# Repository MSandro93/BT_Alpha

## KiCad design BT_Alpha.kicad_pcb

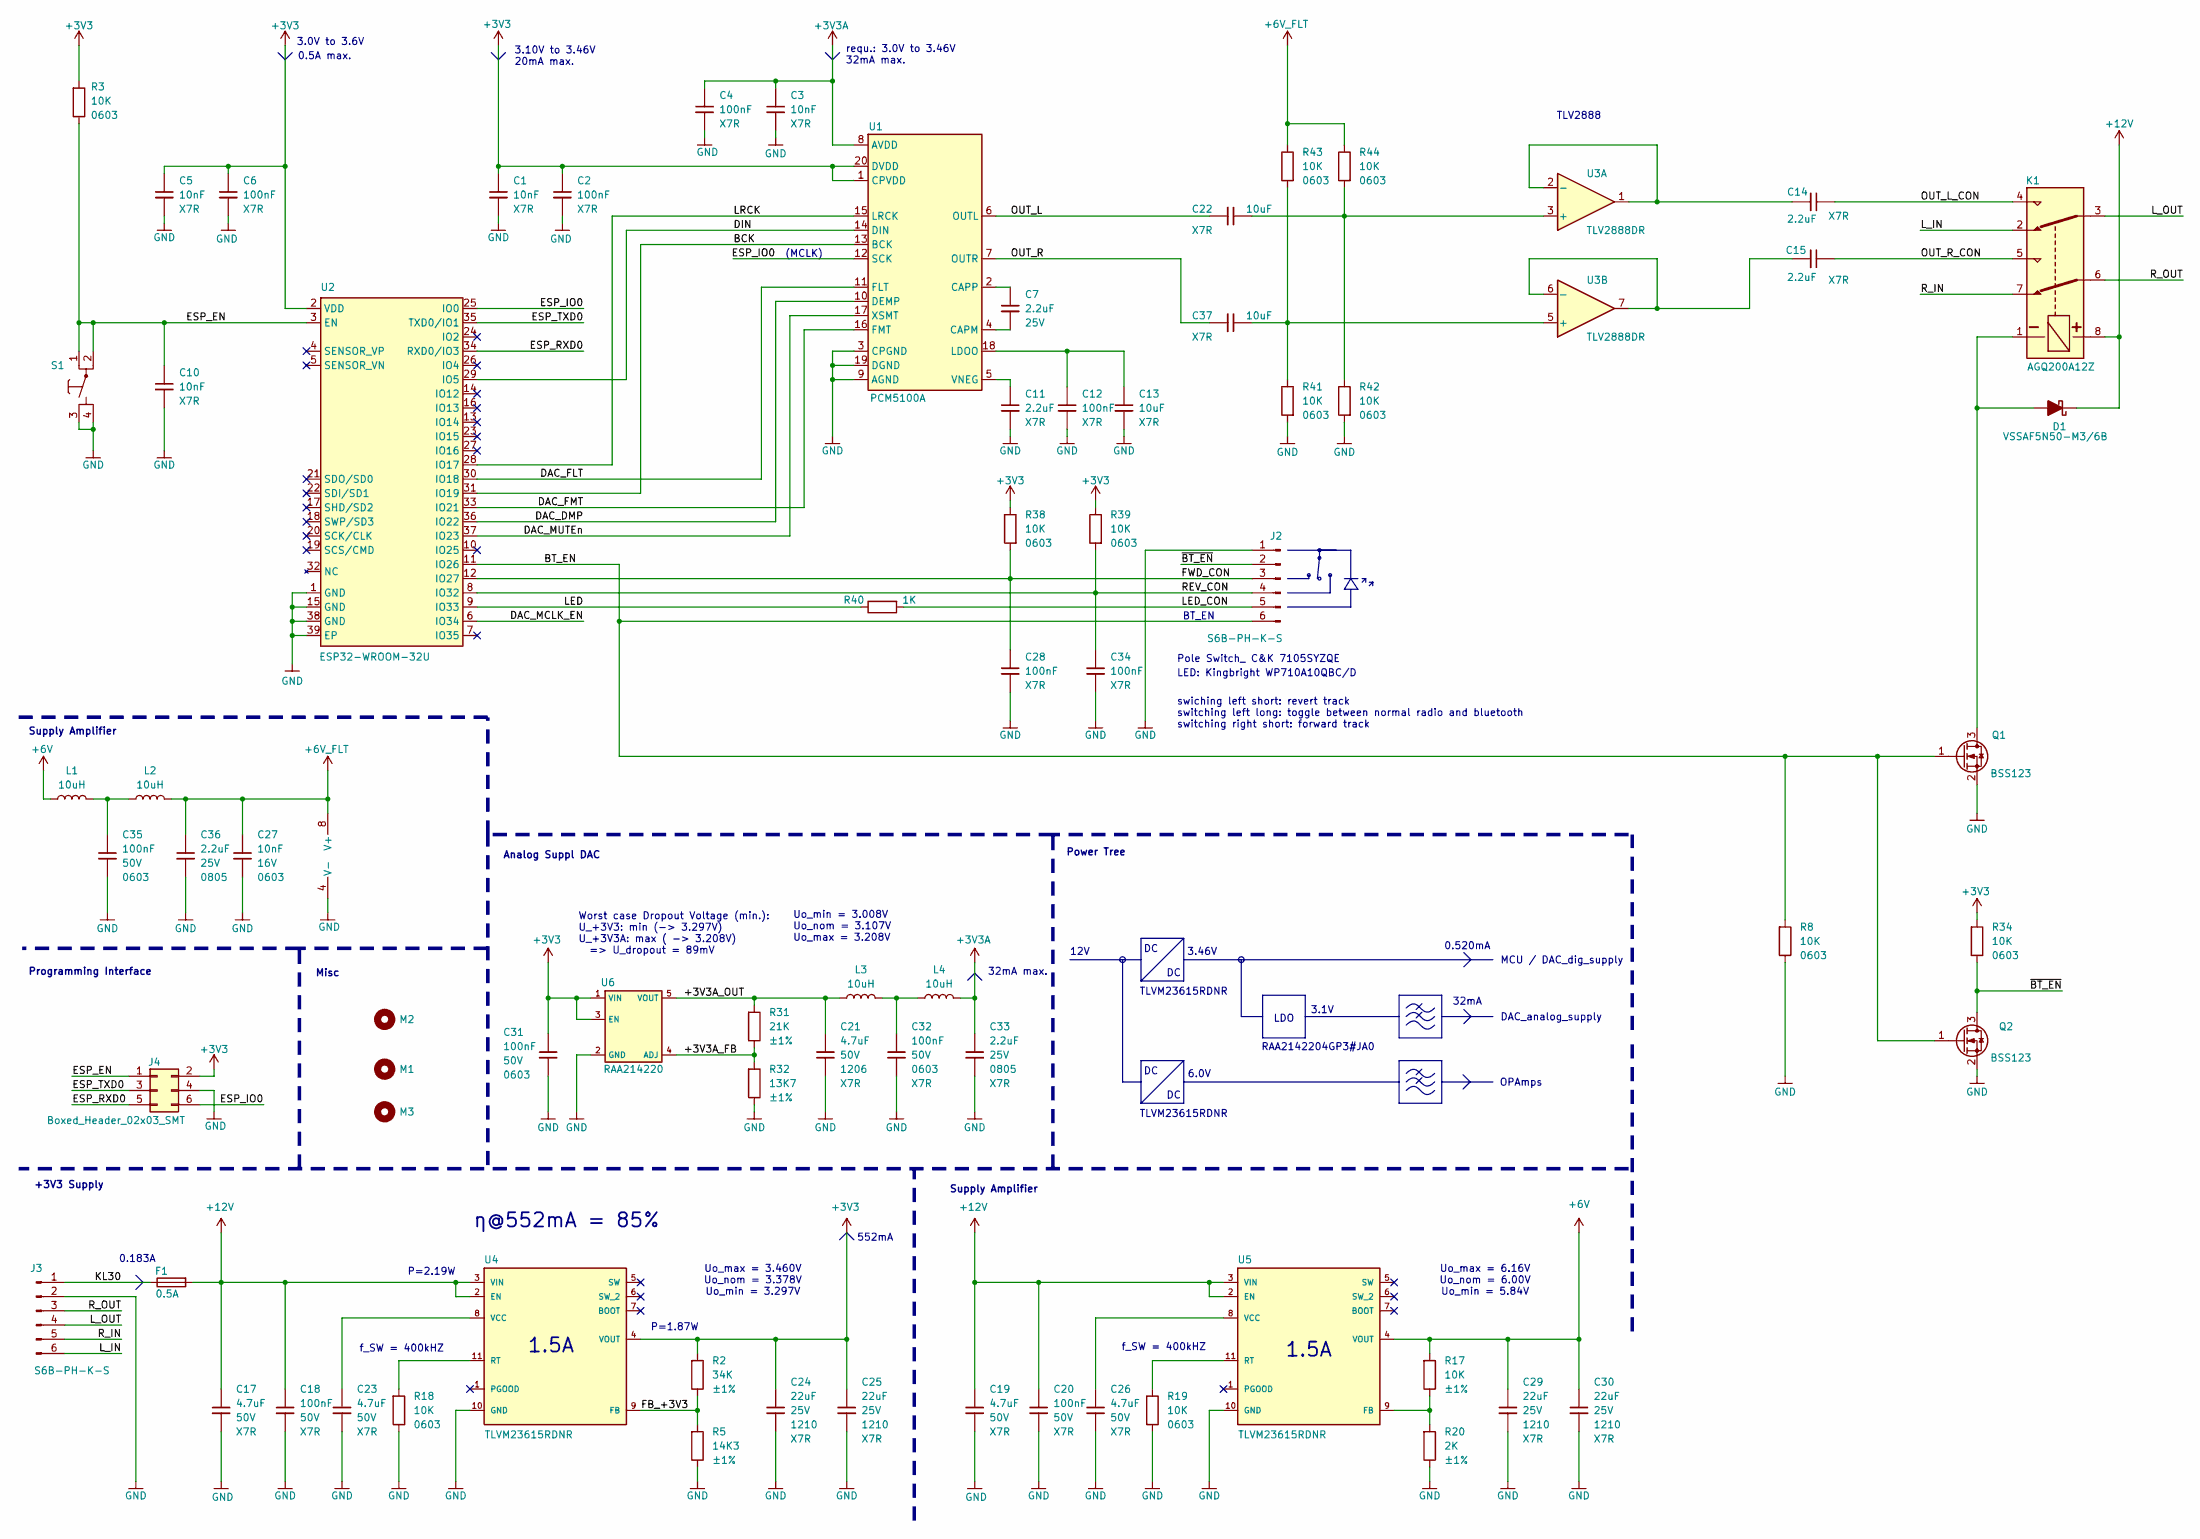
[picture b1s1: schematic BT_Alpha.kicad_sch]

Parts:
C1, C3, C5, C10, C27: 10nF; C_0603; Voltage 16V; Voltage [V] 16; Manufacturer Part Number 0603YC103KAT2A
C2, C4, C6, C12, C18, C20, C28, C31, C32, C34, C35: 100nF; C_0603; Voltage 50V; Voltage [V] 50; Manufacturer Part Number CL10B104KB8NNNC
C7, C11, C14, C15, C33, C36: 2.2uF; C_0805; Voltage 25V; Voltage [V] 25; Manufacturer Part Number CL21B225KAFNNNE
C13, C22, C37: 10uF; C_0805; Voltage 16V; Voltage [V] 16; Manufacturer Part Number CL21B106KOQNNNG
C17, C19, C21, C23, C26: 4.7uF; C_1206; Voltage 50V; Voltage [V] 50; Manufacturer Part Number CL31B475KBHNNNE
C24, C25, C29, C30: 22uF; C_1210; Voltage 25V; Voltage [V] 25; Manufacturer Part Number CL32B105KAFNNNE
D1: VSSAF5N50-M3/6B; VSSAF5N50; Voltage 0.56V; Voltage [V] 0.56; Manufacturer Part Number VSSAF5N50-M3/6B
F1: SF-1206S050-2; SF-1206S; Voltage [V] 63; Voltage 63VDC; Manufacturer Part Number SF-1206S050-2
J2, J3: S6B-PH-K-S; Manufacturer Part Number S6B-PH-K-S
J4: Boxed_Header_02x03_SMT
K1: AGQ200A12Z; AGQ200Axxx; Voltage [V] 12; Voltage 12V; Manufacturer Part Number AGQ200A12Z
L1, L2, L3, L4: 10uH; 74479777310; Manufacturer Part Number 74479777310
M1, M2, M3: Mounting_Hole_2.7mm_Unplated
Q1, Q2: BSS123; Voltage 100V; Voltage [V] 100; Manufacturer Part Number BSS123
R2: 34K; R_0603; Voltage 150V; Voltage [V] 150; Manufacturer Part Number RC0603FR-0734KL
R3, R8, R17, R18, R19, R34, R38, R39, R41, R42, R43, R44: 10K; R_0603; Voltage 150V; Voltage [V] 150; Manufacturer Part Number RC0603FR-0710KL
R5: 14K3; R_0603; Voltage 150V; Voltage [V] 150; Manufacturer Part Number RC0603FR-0714K3L
R20: 2K; R_0603; Voltage 150V; Voltage [V] 150; Manufacturer Part Number RC0603FR-0714K3L
R31: 21K; R_0603; Voltage 150V; Voltage [V] 150; Manufacturer Part Number RC0603FR-0721KL
R32: 13K7; R_0603; Voltage 150V; Voltage [V] 150; Manufacturer Part Number RC0603FR-0713K7L
R40: 1K; R_0603; Voltage 150V; Voltage [V] 150; Manufacturer Part Number RC0603FR-071KL
S1: 434123025826; Manufacturer Part Number 434123025826
U1: PCM5100A; PCM510xx; Manufacturer Part Number PCM5100A
U2: ESP32-WROOM-32U; WROOM_32U; Voltage 3.0 - 3.6; Voltage [V] 3.0V - 3.6V; Manufacturer Part Number ESP32-WROOM-32UE-N8
U3: TLV2888DR; Manufacturer Part Number TLV2888DR
U4, U5: TLVM23615RDNR; TxxM336x5; Manufacturer Part Number TLVM23615RDNR
U6: RAA214220; Manufacturer Part Number RAA2142204GP3#JA0

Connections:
+3V3: C1.1, C2.1, C5.1, C6.1, C24.1, C25.1, C31.1, J4.2, R2.1, R3.1, R34.1, R38.2, R39.2, U1.1 (CPVDD), U1.20 (DVDD), U2.2 (VDD), U4.4 (VOUT), U6.1 (VIN), U6.3 (EN)
+3V3A: C3.1, C4.1, C33.1, L4.2, U1.8 (AVDD)
+6V: C29.1, C30.1, L1.1, R17.1, U5.4 (VOUT)
+6V_FLT: C27.1, C36.1, L2.2, R43.2, R44.2, U3.8 (V+)
+12V: C17.1, C18.1, C19.1, C20.1, D1.K, F1.1, K1.8, U4.2 (EN), U4.3 (VIN), U5.2 (EN), U5.3 (VIN)
/+3V3A_FB: R31.2, R32.1, U6.4 (ADJ)
/+3V3A_OUT: C21.1, L3.1, R31.1, U6.5 (VOUT)
/BCK: U1.13 (BCK), U2.31 (IO19)
/BT_EN: J2.6, Q1.1 (G), Q2.1 (G), R8.1, U2.11 (IO26)
/DAC_DMP: U1.10 (DEMP), U2.36 (IO22)
/DAC_FLT: U1.11 (FLT), U2.30 (IO18)
/DAC_FMT: U1.16 (FMT), U2.33 (IO21)
/DAC_MCLK_EN: U2.6 (IO34)
/DAC_MUTEn: U1.17 (XSMT), U2.37 (IO23)
/DIN: U1.14 (DIN), U2.29 (IO5)
/ESP_EN: C10.1, J4.1, R3.2, S1.1, S1.2, U2.3 (EN)
/ESP_IO0: J4.6, U1.12 (SCK), U2.25 (IO0)
/ESP_RXD0: J4.5, U2.34 (RXD0/IO3)
/ESP_TXD0: J4.3, U2.35 (TXD0/IO1)
/FB_+3V3: R2.2, R5.1, U4.9 (FB)
/FWD_CON: C28.1, J2.3, R38.1, U2.12 (IO27)
/KL30: F1.2, J3.1
/LED: R40.2, U2.9 (IO33)
/LED_CON: J2.5, R40.1
/LRCK: U1.15 (LRCK), U2.28 (IO17)
/L_IN: J3.6, K1.2
/L_OUT: J3.4, K1.3
/OUT_L: C22.2, U1.6 (OUTL)
/OUT_L_CON: C14.1, K1.4
/OUT_R: C37.2, U1.7 (OUTR)
/OUT_R_CON: C15.1, K1.5
/REV_CON: C34.1, J2.4, R39.1, U2.8 (IO32)
/R_IN: J3.5, K1.7
/R_OUT: J3.3, K1.6
/~BT_EN: J2.2, Q2.3 (D), R34.2
GND: C1.2, C2.2, C3.2, C4.2, C5.2, C6.2, C10.2, C11.2, C12.2, C13.2, C17.2, C18.2, C19.2, C20.2, C21.2, C23.2, C24.2, C25.2, C26.2, C27.2, C28.2, C29.2, C30.2, C31.2, C32.2, C33.2, C34.2, C35.2, C36.2, J2.1, J3.2, J4.4, Q1.2 (S), Q2.2 (S), R5.2, R8.2, R18.2, R19.2, R20.2, R32.2, R41.1, R42.1, S1.3, S1.4, U1.3 (CPGND), U1.9 (AGND), U1.19 (DGND), U2.1 (GND), U2.15 (GND), U2.38 (GND), U2.39 (EP), U3.4 (V-), U4.10 (GND), U5.10 (GND), U6.2 (GND)
unnamed: C32.1, L3.2, L4.1
unnamed: C35.1, L1.2, L2.1
unnamed: D1.A, K1.1, Q1.3 (D)
unnamed: C7.2, U1.4 (CAPM)
unnamed: C7.1, U1.2 (CAPP)
unnamed: C12.1, C13.1, U1.18 (LDOO)
unnamed: C11.1, U1.5 (VNEG)
unnamed: C22.1, R42.2, R44.1, U3.3 (+)
unnamed: C14.2, U3.1, U3.2 (-)
unnamed: C37.1, R41.2, R43.1, U3.5 (+)
unnamed: C15.2, U3.6 (-), U3.7
unnamed: R18.1, U4.11 (RT)
unnamed: C23.1, U4.8 (VCC)
unnamed: R17.2, R20.1, U5.9 (FB)
unnamed: R19.1, U5.11 (RT)
unnamed: C26.1, U5.8 (VCC)

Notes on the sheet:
32mA
Supply Amplifier
Worst case Dropout Voltage (min.): U_+3V3: min (-> 3.297V) U_+3V3A: max ( -> 3.208V) => U_dropout = 89mV
DAC_analog_supply
Misc
32mA max.
1.5A
MCU / DAC_dig_supply
Power Tree
f_SW = 400kHZ
0.183A
requ.: 3.0V to 3.46V 32mA max.
Uo_min = 3.008V Uo_nom = 3.107V Uo_max = 3.208V
RAA2142204GP3#JA0
OPAmps
0.520mA
BT_EN
P=2.19W
552mA
0.5A max.
η@552mA = 85%
LED: Kingbright WP710A10QBC/D
Pole Switch_ C&K 7105SYZQE
+3V3 Supply
Uo_max = 6.16V Uo_nom = 6.00V Uo_min = 5.84V
3.10V to 3.46V 20mA max.
Uo_max = 3.460V Uo_nom = 3.378V Uo_min = 3.297V
(MCLK)
TLVM23615RDNR
3.1V
LDO
6.0V
TLV2888
P=1.87W
3.0V to 3.6V
swiching left short: revert track switching left long: toggle between normal radio and bluetooth switching right short: forward track
12V
Programming Interface
Analog Suppl DAC
3.46V

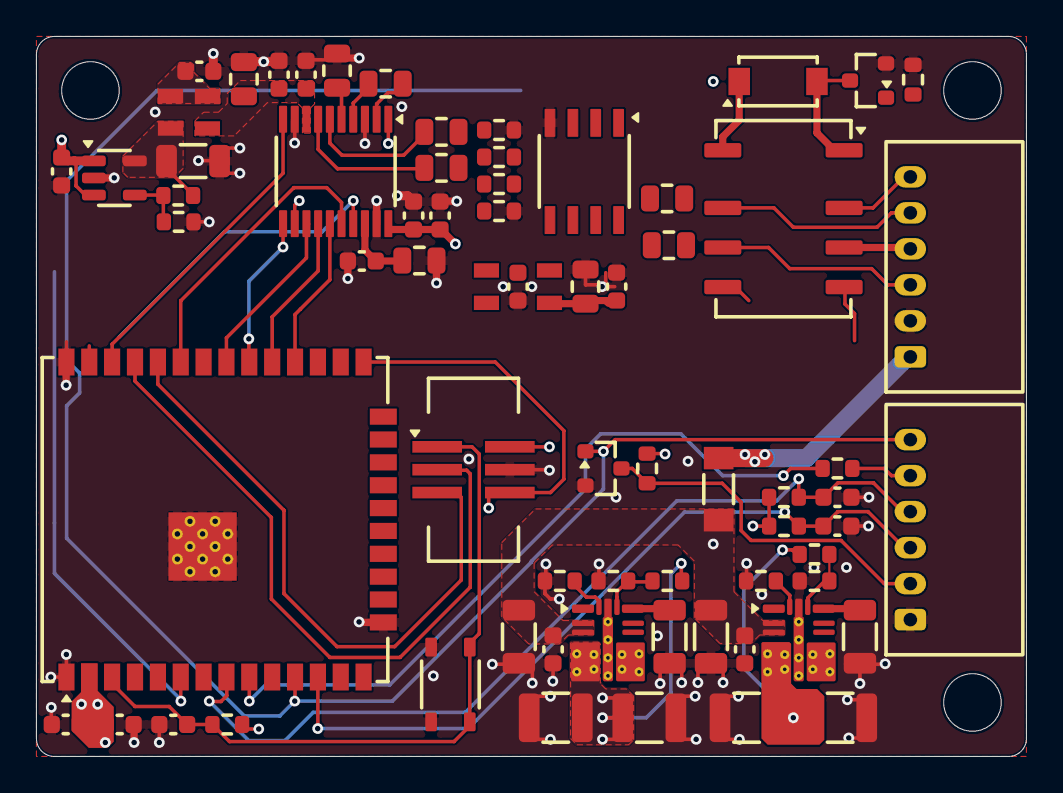
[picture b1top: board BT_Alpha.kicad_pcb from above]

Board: 4 copper layers, 55.0 x 40.0 mm, 74 parts (0 on the bottom side), 51 nets.

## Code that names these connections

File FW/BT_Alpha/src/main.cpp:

/*
  Streaming Music from Bluetooth
  
  Copyright (C) 2020 Phil Schatzmann
  This program is free software: you can redistribute it and/or modify
  it under the terms of the GNU General Public License as published by
  the Free Software Foundation, either version 3 of the License, or
  (at your option) any later version.
  This program is distributed in the hope that it will be useful,
  but WITHOUT ANY WARRANTY; without even the implied warranty of
  MERCHANTABILITY or FITNESS FOR A PARTICULAR PURPOSE.  See the
  GNU General Public License for more details.
  You should have received a copy of the GNU General Public License
  along with this program.  If not, see <http://www.gnu.org/licenses/>.
*/

 //==> Example which shows how to use the built in ESP32 I2S < 3.0.0



 // Cedits to: Phil Schatzmann (https://github.com/pschatzmann/ESP32-A2DP/tree/main)



#include <Arduino.h>
#include "BluetoothA2DPSink.h"
#include "AudioTools.h"

#define FWD 27
#define REV 32
#define LED 33
#define BT_EN 26
#define DAC_MCLK_EN 34
#define DAC_MUTEn 23
#define DAC_DMP 22
#define DAC_FMT 21
#define DAC_FLT 18
#define MCLK 16

I2SStream i2s;
BluetoothA2DPSink a2dp_sink(i2s);

int state = 0;
int timer_cnt = 0;
int switched_to_BT = 0;

void GPIO_Init()
{
  pinMode(FWD, INPUT);
  pinMode(REV, INPUT);
  pinMode(LED, OUTPUT);
  pinMode(BT_EN, OUTPUT);
  pinMode(DAC_DMP, OUTPUT);
  pinMode(DAC_FMT, OUTPUT);
  pinMode(DAC_MUTEn, OUTPUT);
  pinMode(DAC_FLT, OUTPUT);
}


void setup()
{
  disableCore0WDT();

  digitalWrite(DAC_MUTEn, 0);

  Serial.begin(115200);
  GPIO_Init();

  auto cfg = i2s.defaultConfig();
  cfg.pin_bck = 19;
  cfg.pin_ws = 17;
  cfg.pin_data = 5;
  cfg.pin_mck = 0;
  cfg.bits_per_sample = 16;
  cfg.sample_rate = 44100;
  cfg.i2s_format = I2S_STD_FORMAT;

  if (!i2s.begin(cfg))
  {
      Serial.print("Failed to initialize I2S!");
      Serial.print("\r\n");
      while (1); // do nothing
  }

    a2dp_sink.set_auto_reconnect(true, 3);

    state = 0;
    timer_cnt = 0;
}


void setState(int s_)
{
  state = s_;
  Serial.print(state);
  Serial.print("\r\n");
}


void loop()
{
  switch(state)
  {
    case 0: //idle
    {
      if((digitalRead(REV) == 1)  && (digitalRead(FWD) == 0))
      {
        setState(1);
      }
      else if((digitalRead(FWD) == 1) && (digitalRead(REV) == 0))
      {
        setState(2);
      }
      break;
    }

    case 1: //is holded left
    {
      timer_cnt++;

      if(timer_cnt >= 40) // was pressed long
        {
          if(switched_to_BT == 0) //currently switched to normal radio
          {
            switched_to_BT = 1;
            digitalWrite(BT_EN, 1);      
            digitalWrite(LED, 1);    
            a2dp_sink.start("BT Alpha");
            digitalWrite(DAC_MUTEn, 1); //unmute
            setState(3);
          }
          else
          {
            digitalWrite(DAC_MUTEn, 0);  //mute
            switched_to_BT = 0;
            digitalWrite(BT_EN, 0);
            a2dp_sink.disconnect();
            digitalWrite(LED, 0);
            setState(3);
          }
          timer_cnt = 0;
          break;
        }

      else if((digitalRead(REV)) == 1 && (digitalRead(FWD) == 1)) 
      {
        if (a2dp_sink.is_connected() == true) // was pressed short
        {
          a2dp_sink.previous();
          setState(0);
          Serial.print("a");
        }    
        break;
      }
    }


    case 2:  //next
    {
      if((digitalRead(REV)) == 1 && (digitalRead(FWD) == 1))
      {
        if (a2dp_sink.is_connected() == true)
        {
          a2dp_sink.next();
          setState(0);
        }
      }
      break;
    }

    case 3:
    {
      if((digitalRead(REV)) == 1 && (digitalRead(FWD) == 1))
      {
        setState(0);
      }
      break;
    }
  }

  delay(50);
}

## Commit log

2026-03-25 init
2026-03-26 rough placement
2026-03-26 added comment
2026-03-27 added amplifier. So control volume by knob, signal has to be in injected before the volume control poti. This is why around 5V signal amplitude are necessary.
2026-03-28 Increased intermediate rail from 5 to 6V; replaced LDO for diigital supply by DCDC
2026-03-28 clean up
2026-03-28 integrated DAC in database
2026-03-30 rough placement PSU
2026-04-03 replaced all components by library parts
2026-04-03 started layout
2026-04-04 almost finished layout. Something is still off in the design rules
2026-04-04 added teardrops
2026-04-10 added signals
2026-04-11 Release Rev. A
2026-04-11 renamed project
2026-04-11 Updated Jobset
2026-04-18 added iBoM
2026-04-21 rounded edges
2026-04-28 started iterating to rev. B
2026-04-28 added FW; updated gitignore
2026-04-28 added credits
2026-04-30 fixed state machine
2026-05-01 diameter
2026-05-01 added dimensioning for mounting hole diameter
